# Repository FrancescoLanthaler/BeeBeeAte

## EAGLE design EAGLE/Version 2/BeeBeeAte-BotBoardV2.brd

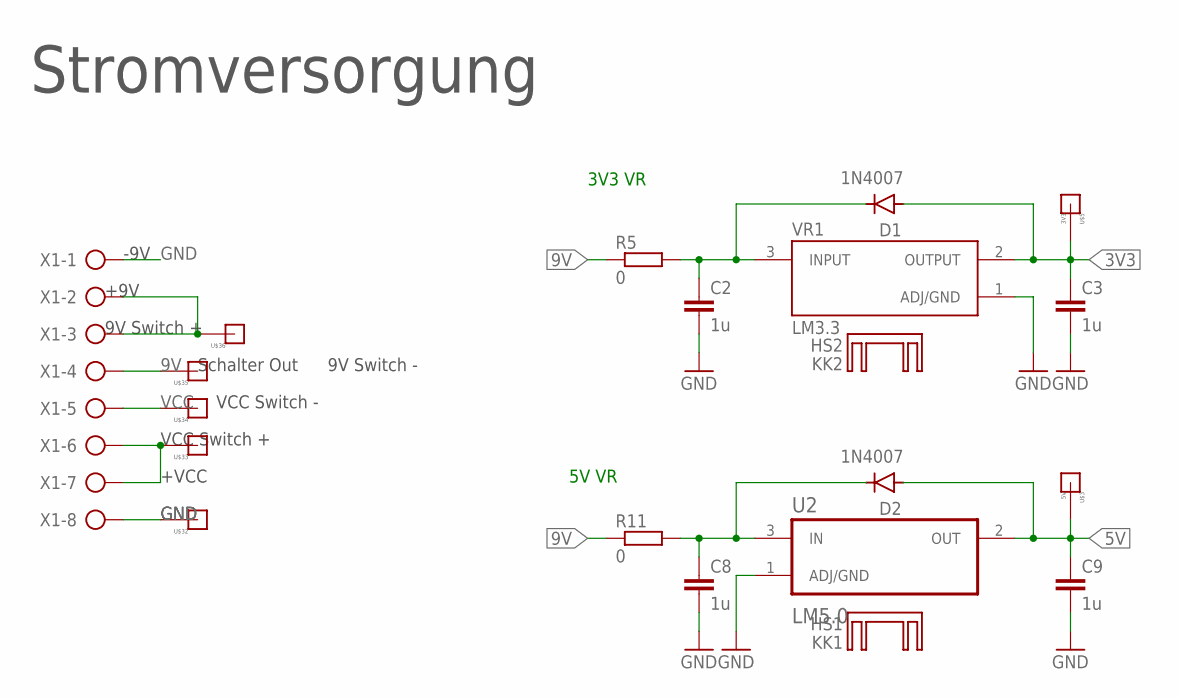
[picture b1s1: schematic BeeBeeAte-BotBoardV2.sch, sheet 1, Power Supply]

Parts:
C2, C3, C8, C9: 1u; C0805
D1, D2: 1N4007; DO-41
KK1: HS1; SK95-2M3
KK2: HS2; SK95-2M3
R5, R11: 0; R0805
U2: LM5.0; TO254P1054X470X1955-3
U$3: 5V; MESSPAD
U$5: 3V3; MESSPAD
U$32, U$33, U$34, U$35, U$36: MESSPAD
VR1: LM3.3; TO254P1054X470X1955-3
X1: +9V; AK300/8

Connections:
3V3: C3.1, D1.A, U$5.MSP, VR1.2 (OUTPUT); also elsewhere on the board
5V: C9.1, D2.A, U2.2 (OUT), U$3.MSP; also elsewhere on the board
9V: R5.1, R11.1, U$35.MSP, X1.4
+VCC: U$33.MSP, X1.6, X1.7
GND: C2.2, C3.2, C8.2, C9.2, U2.1 (ADJ/GND), U$32.MSP, VR1.1 (ADJ/GND), X1.1, X1.8; also elsewhere on the board
unnamed: C2.1, D1.C, R5.2, VR1.3 (INPUT)
unnamed: C8.1, D2.C, R11.2, U2.3 (IN)
unnamed: U$36.MSP, X1.2, X1.3
VCC: U$34.MSP, X1.5; also elsewhere on the board

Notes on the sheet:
5V VR
3V3 VR
Stromversorgung
Schalter Out
9V Switch +
9V Switch -
+9V
-9V
VCC Switch -
+VCC
VCC Switch +

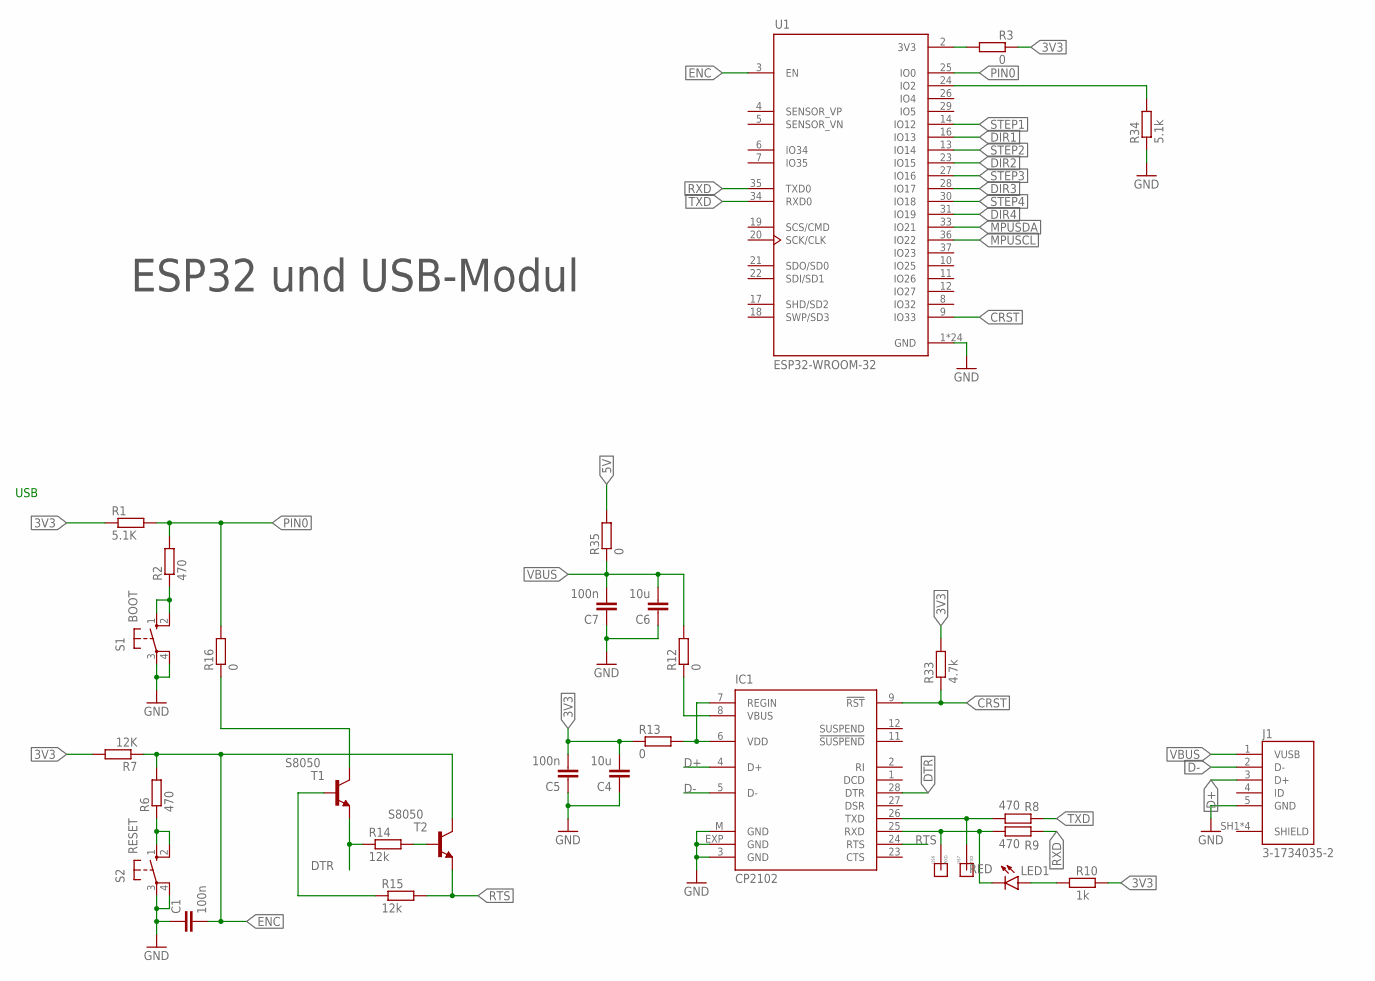
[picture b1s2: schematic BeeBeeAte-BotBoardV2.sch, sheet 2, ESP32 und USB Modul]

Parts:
C1, C5, C7: 100n; C0805
C4, C6: 10u; C0805
IC1: CP2102; MLP28
J1: 3-1734035-2; TE_3-1734035-2
LED1: RED; CHIP-LED0805
R1: 5.1K; R0805
R2, R6, R8, R9: 470; R0805
R3, R12, R13, R16, R35: 0; R0805
R7: 12K; R0805
R10: 1k; R0805
R14, R15: 12k; R0805
R33: 4.7k; R0805
R34: 5.1k; R0805
S1: BOOT; B3F-10XX
S2: RESET; B3F-10XX
T1, T2: S8050; SOT23-BEC
U1: ESP32-WROOM-32; MODULE_ESP32-WROOM-32
U$6: RXD; MESSPAD
U$7: TXD; MESSPAD

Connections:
3V3: C4.2, C5.2, R1.1, R3.2, R7.2, R10.2, R13.1, R33.2; also elsewhere on the board
5V: R35.2; also elsewhere on the board
CRST: IC1.9 (!RST), R33.1, U1.9 (IO33)
D+: IC1.4 (D+), J1.3 (D+)
D-: IC1.5 (D-), J1.2 (D-)
DIR1: U1.16 (IO13); also elsewhere on the board
DIR2: U1.23 (IO15); also elsewhere on the board
DIR3: U1.28 (IO17); also elsewhere on the board
DIR4: U1.31 (IO19); also elsewhere on the board
DTR: IC1.28 (DTR), R14.1, T1.E
ENC: C1.2, R6.2, R7.1, T2.C, U1.3 (EN)
GND: C1.1, C4.1, C5.1, C6.1, C7.1, IC1.3 (GND), IC1.EXP (GND), IC1.M (GND), J1.5 (GND), R34.1, S1.3, S1.4 (P1), S2.3, S2.4 (P1), U1.1 (GND), U1.15 (GND), U1.38 (GND), U1.39_1 (GND), U1.39_2 (GND), U1.39_3 (GND), U1.39_4 (GND), U1.39_5 (GND), U1.39_6 (GND), U1.39_7 (GND), U1.39_8 (GND), U1.39_9 (GND), U1.39_10 (GND), U1.39_11 (GND), U1.39_12 (GND), U1.39_13 (GND), U1.39_14 (GND), U1.39_15 (GND), U1.39_16 (GND), U1.39_17 (GND), U1.39_18 (GND), U1.39_19 (GND), U1.39_20 (GND), U1.39_21 (GND); also elsewhere on the board
MPUSCL: U1.36 (IO22); also elsewhere on the board
MPUSDA: U1.33 (IO21); also elsewhere on the board
unnamed: R2.1, S1.1 (S), S1.2 (S1)
unnamed: R6.1, S2.1 (S), S2.2 (S1)
unnamed: IC1.25 (RXD), LED1.C, R9.1, U$6.MSP
unnamed: LED1.A, R10.1
unnamed: IC1.26 (TXD), R8.1, U$7.MSP
unnamed: IC1.6 (VDD), IC1.7 (REGIN), R13.2
unnamed: IC1.8 (VBUS), R12.1
unnamed: R14.2, T2.B
unnamed: R15.1, T1.B
unnamed: R34.2, U1.24 (IO2)
unnamed: R3.1, U1.2 (3V3)
PIN0: R1.2, R2.2, R16.2, U1.25 (IO0)
PIN1: R16.1, T1.C
RTS: IC1.24 (RTS), R15.2, T2.E
RXD: R9.2, U1.35 (TXD0)
STEP1: U1.14 (IO12); also elsewhere on the board
STEP2: U1.13 (IO14); also elsewhere on the board
STEP3: U1.27 (IO16); also elsewhere on the board
STEP4: U1.30 (IO18); also elsewhere on the board
TXD: R8.2, U1.34 (RXD0)
VBUS: C6.2, C7.2, J1.1 (VUSB), R12.2, R35.1

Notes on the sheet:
USB
ESP32 und USB-Modul

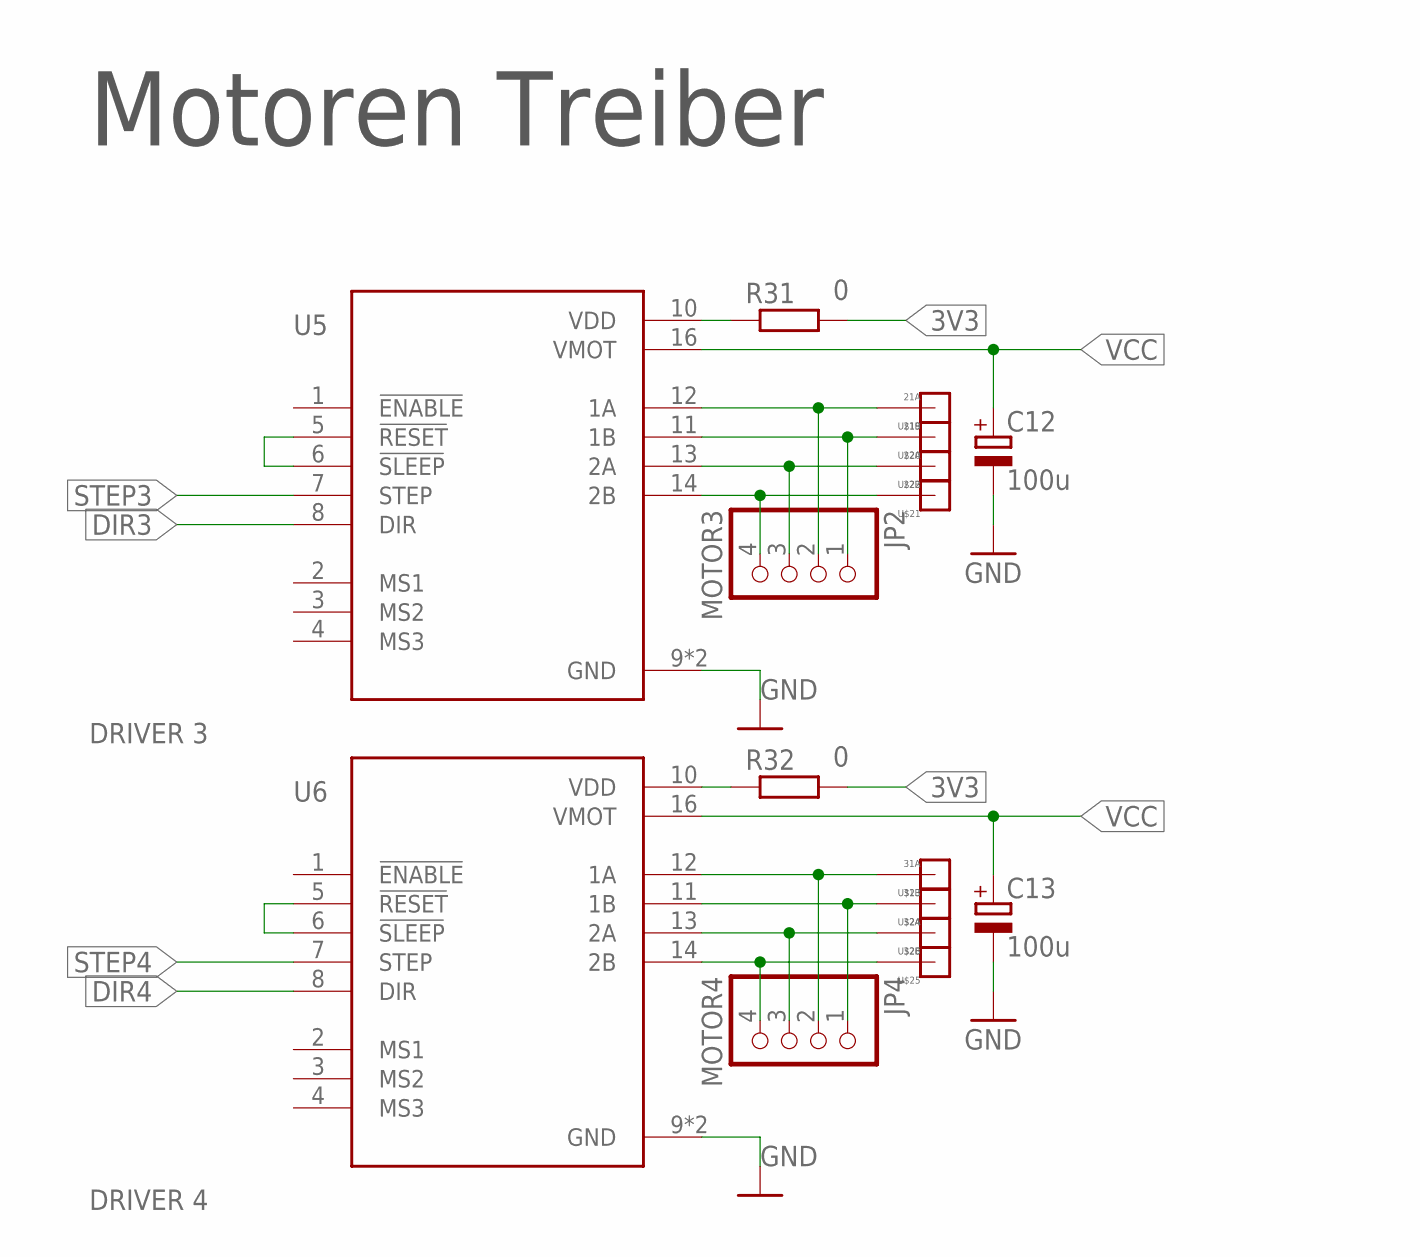
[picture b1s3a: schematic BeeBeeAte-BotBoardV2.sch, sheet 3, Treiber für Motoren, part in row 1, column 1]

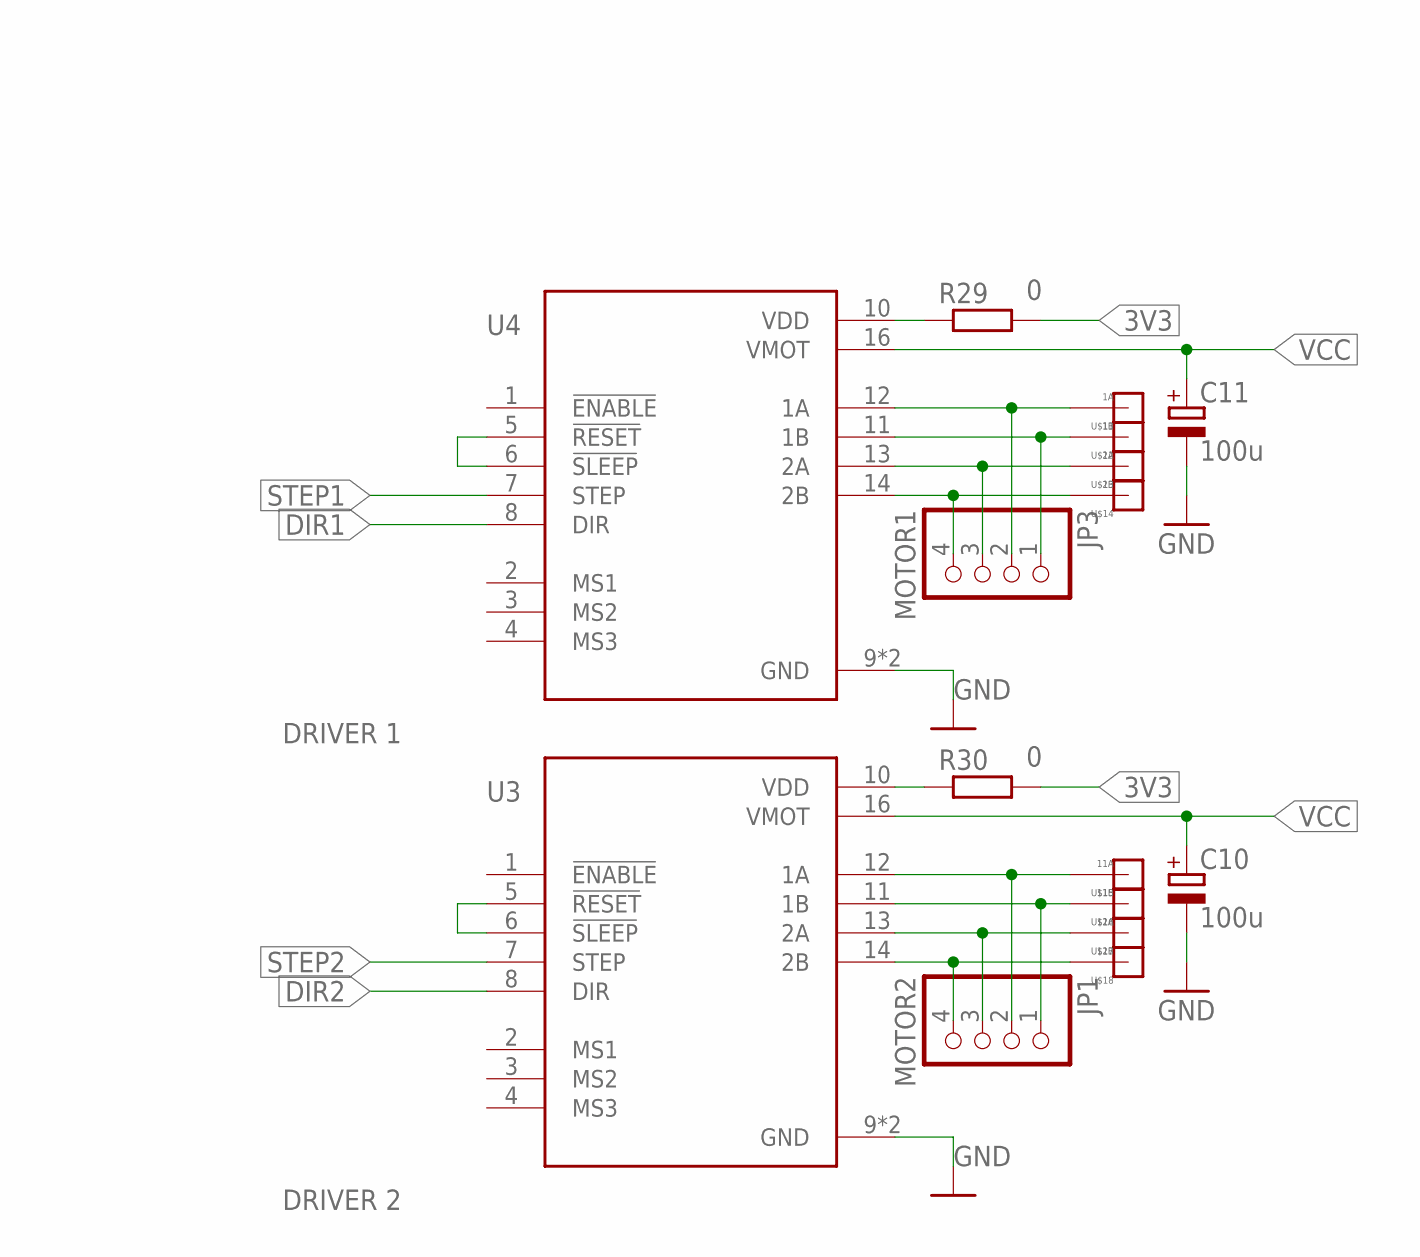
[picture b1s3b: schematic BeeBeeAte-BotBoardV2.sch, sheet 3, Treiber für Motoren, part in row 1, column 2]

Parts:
C10, C11, C12, C13: 100u; 153CLV-0605
JP1: MOTOR2; 1X04
JP2: MOTOR3; 1X04
JP3: MOTOR1; 1X04
JP4: MOTOR4; 1X04
R29, R30, R31, R32: 0; R0805
U3: DRIVER 2; MODULE_A4988_STEPPER_MOTOR_DRIVER_CARRIER
U4: DRIVER 1; MODULE_A4988_STEPPER_MOTOR_DRIVER_CARRIER
U5: DRIVER 3; MODULE_A4988_STEPPER_MOTOR_DRIVER_CARRIER
U6: DRIVER 4; MODULE_A4988_STEPPER_MOTOR_DRIVER_CARRIER
U$11: 1A; MESSPAD
U$12: 1B; MESSPAD
U$13: 2A; MESSPAD
U$14: 2B; MESSPAD
U$15: 11A; MESSPAD
U$16: 11B; MESSPAD
U$17: 12A; MESSPAD
U$18: 12B; MESSPAD
U$19: 21A; MESSPAD
U$20: 21B; MESSPAD
U$21: 22B; MESSPAD
U$22: 22A; MESSPAD
U$23: 31A; MESSPAD
U$24: 31B; MESSPAD
U$25: 32B; MESSPAD
U$26: 32A; MESSPAD

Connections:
3V3: R29.2, R30.2, R31.2, R32.2; also elsewhere on the board
DIR1: U4.8 (DIR); also elsewhere on the board
DIR2: U3.8 (DIR); also elsewhere on the board
DIR3: U5.8 (DIR); also elsewhere on the board
DIR4: U6.8 (DIR); also elsewhere on the board
GND: C10.-, C11.-, C12.-, C13.-, U3.9 (GND), U3.15 (GND), U4.9 (GND), U4.15 (GND), U5.9 (GND), U5.15 (GND), U6.9 (GND), U6.15 (GND); also elsewhere on the board
unnamed: R30.1, U3.10 (VDD)
unnamed: JP1.2, U3.12 (1A), U$15.MSP
unnamed: JP1.1, U3.11 (1B), U$16.MSP
unnamed: JP1.3, U3.13 (2A), U$17.MSP
unnamed: JP1.4, U3.14 (2B), U$18.MSP
unnamed: U3.5 (!RESET), U3.6 (!SLEEP)
unnamed: R29.1, U4.10 (VDD)
unnamed: JP2.2, U5.12 (1A), U$19.MSP
unnamed: JP2.1, U5.11 (1B), U$20.MSP
unnamed: JP2.3, U5.13 (2A), U$22.MSP
unnamed: JP2.4, U5.14 (2B), U$21.MSP
unnamed: JP3.2, U4.12 (1A), U$11.MSP
unnamed: JP3.1, U4.11 (1B), U$12.MSP
unnamed: JP3.3, U4.13 (2A), U$13.MSP
unnamed: U5.5 (!RESET), U5.6 (!SLEEP)
unnamed: R31.1, U5.10 (VDD)
unnamed: R32.1, U6.10 (VDD)
unnamed: JP3.4, U4.14 (2B), U$14.MSP
unnamed: U4.5 (!RESET), U4.6 (!SLEEP)
unnamed: JP4.2, U6.12 (1A), U$23.MSP
unnamed: JP4.1, U6.11 (1B), U$24.MSP
unnamed: JP4.3, U6.13 (2A), U$26.MSP
unnamed: JP4.4, U6.14 (2B), U$25.MSP
unnamed: U6.5 (!RESET), U6.6 (!SLEEP)
STEP1: U4.7 (STEP); also elsewhere on the board
STEP2: U3.7 (STEP); also elsewhere on the board
STEP3: U5.7 (STEP); also elsewhere on the board
STEP4: U6.7 (STEP); also elsewhere on the board
VCC: C10.+, C11.+, C12.+, C13.+, U3.16 (VMOT), U4.16 (VMOT), U5.16 (VMOT), U6.16 (VMOT); also elsewhere on the board

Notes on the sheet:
Motoren Treiber

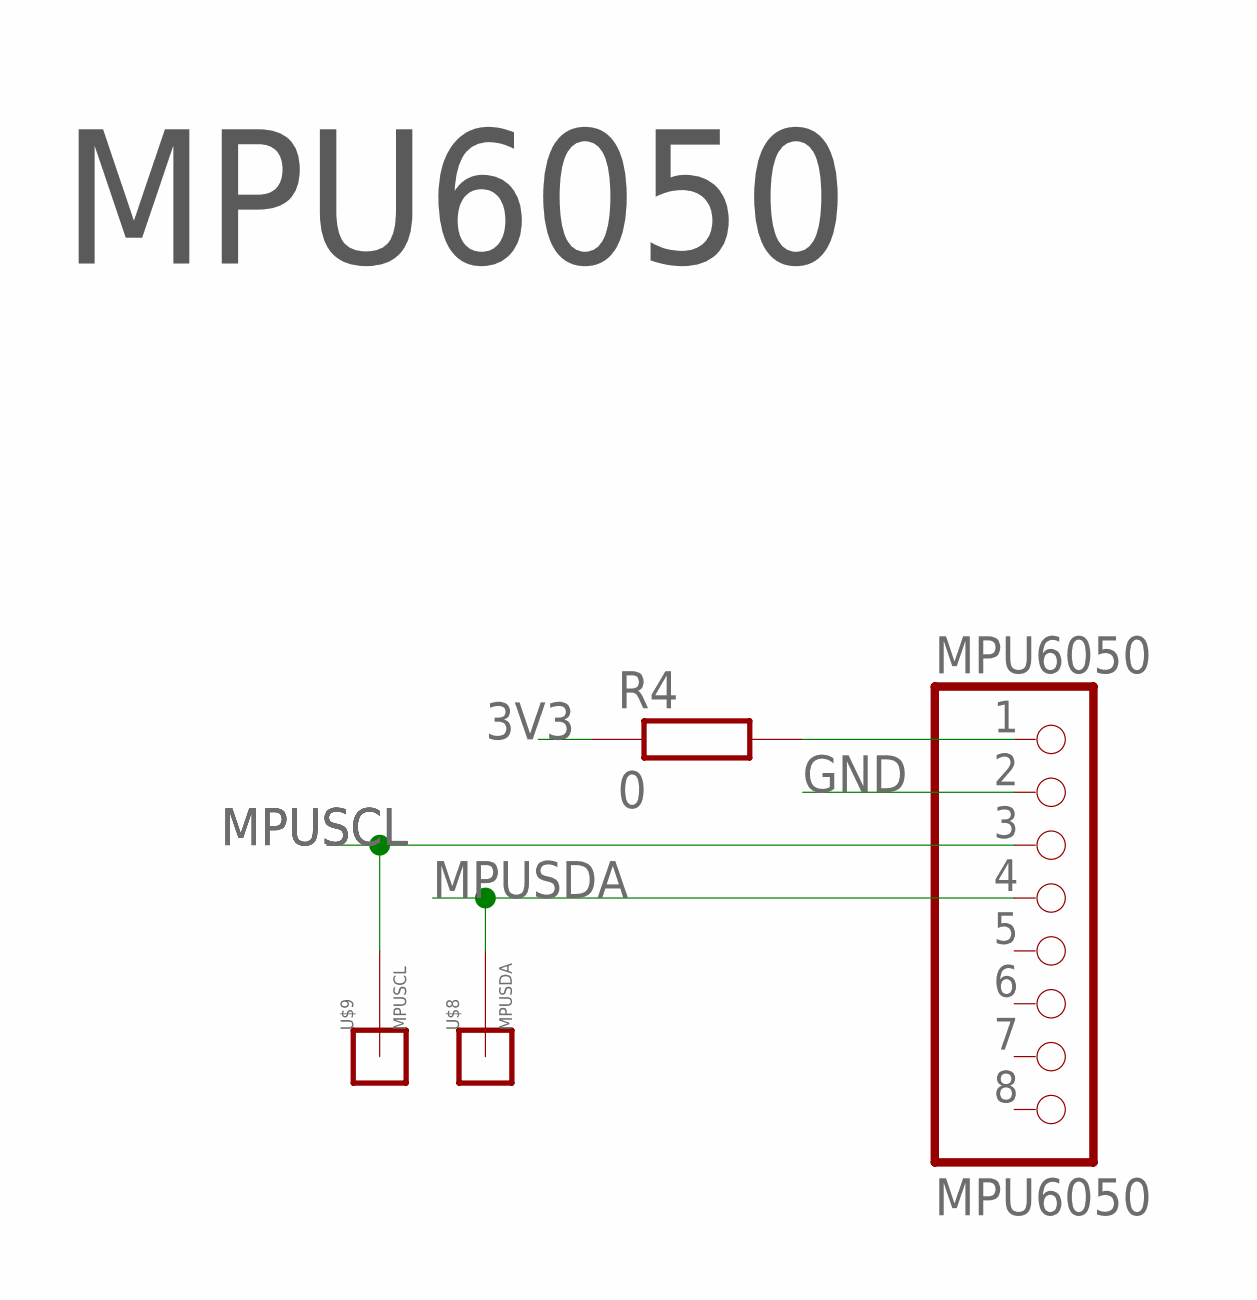
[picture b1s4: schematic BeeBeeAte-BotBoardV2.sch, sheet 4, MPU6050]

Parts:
MPU6050: MPU6050; 1X08
R4: 0; R0805
U$8: MPUSDA; MESSPAD
U$9: MPUSCL; MESSPAD

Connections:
3V3: R4.1; also elsewhere on the board
GND: MPU6050.2; also elsewhere on the board
MPUSCL: MPU6050.3, U$9.MSP; also elsewhere on the board
MPUSDA: MPU6050.4, U$8.MSP; also elsewhere on the board
unnamed: MPU6050.1, R4.2

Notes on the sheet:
MPU6050

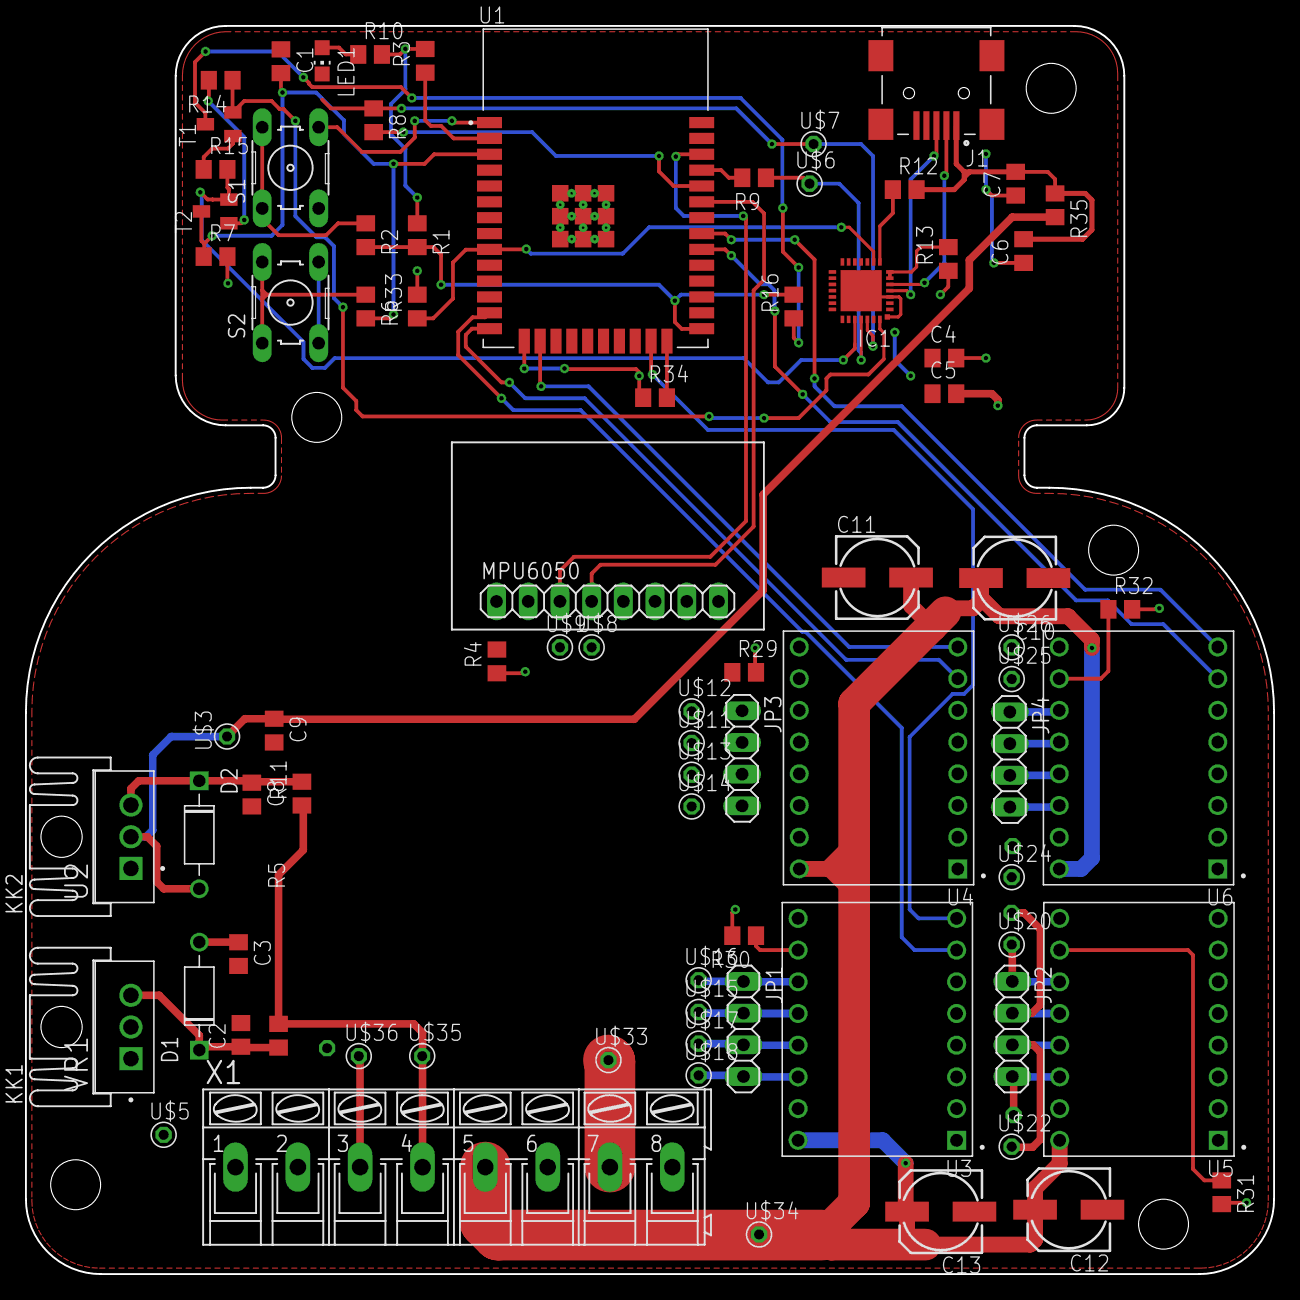
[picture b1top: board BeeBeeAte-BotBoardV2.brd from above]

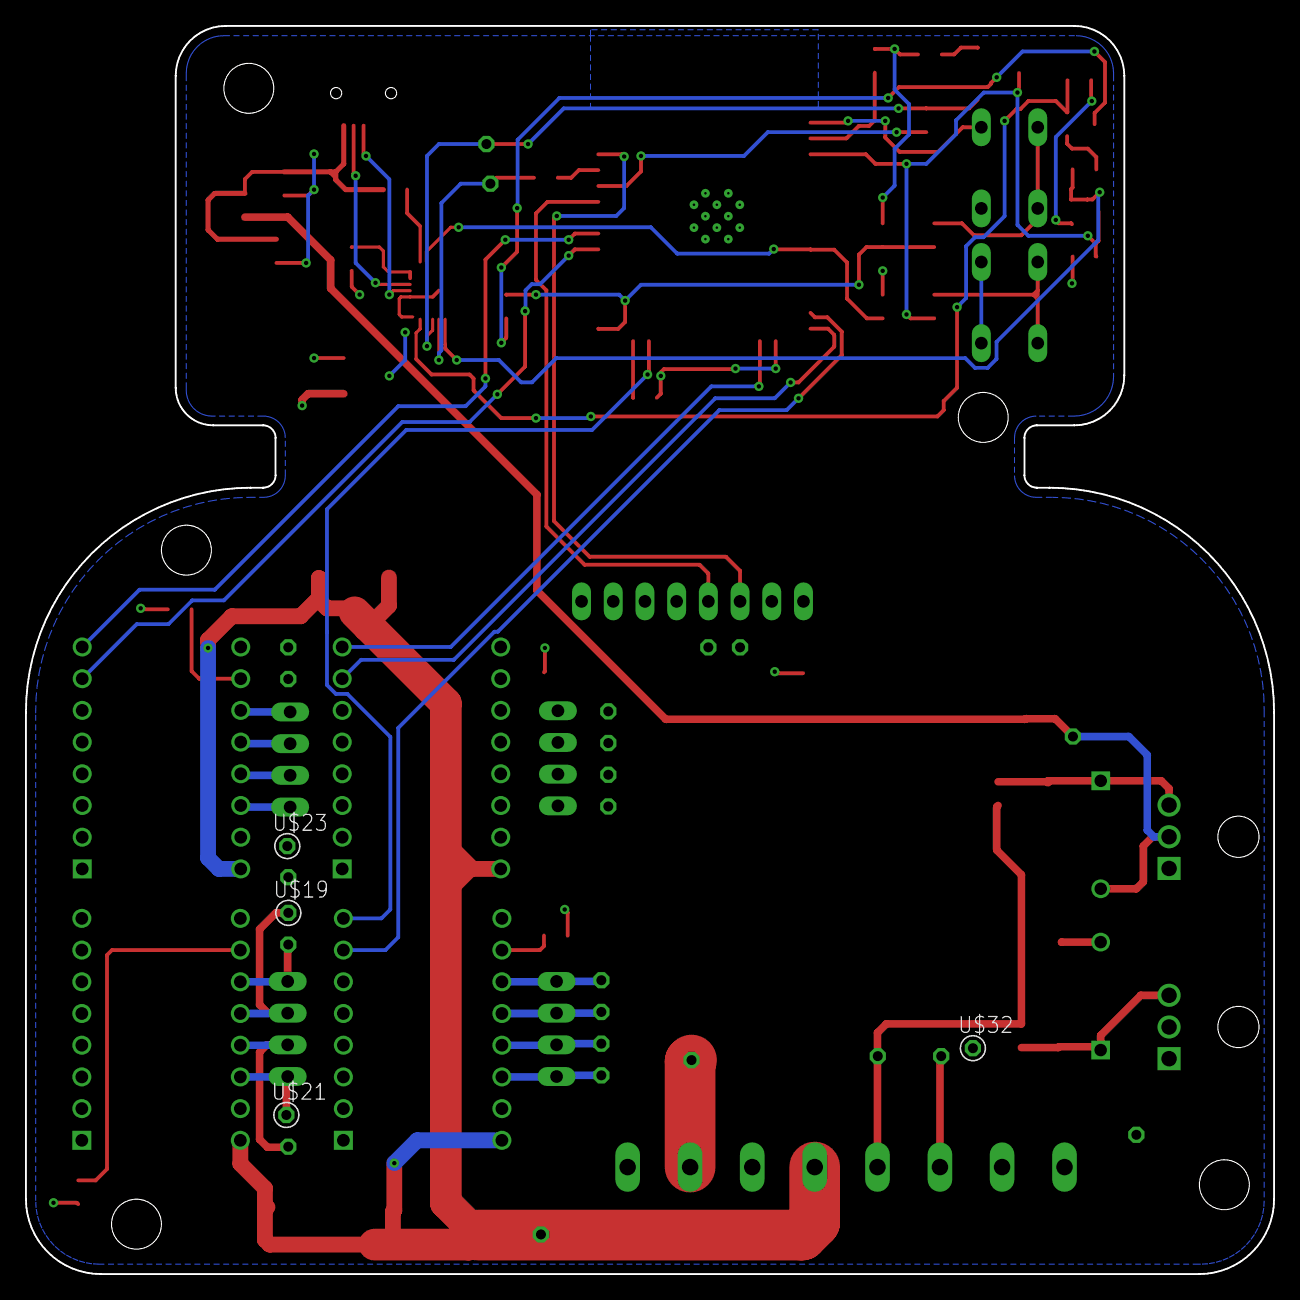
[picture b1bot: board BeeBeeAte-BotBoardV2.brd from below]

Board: 2 copper layers, 100.0 x 100.0 mm, 87 parts (4 on the bottom side), 66 nets.

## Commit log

2021-10-26 First remote
2021-10-26 Renaming files
2021-10-26 Added Remote
2021-10-26 added gitignore
2021-10-26 Border put in milling layer
2021-10-27 Completed BOM and CPL
2021-10-27 Changed Gerber File to tValue
2021-10-27 Added Logo to remote and created GERBER, BOM and CPL for remote
2021-10-28 temp file
2021-11-01 Added 3,7V battery
2021-11-06 Added 3D Files and modified Board
2021-11-08 Checked by teacher and fixed
2021-11-17 MILESTONE: PCB Ordered
2021-12-13 Added Code
2021-12-13 Added Header files (errors)
2021-12-15 Added Motors
2021-12-15 Added Motorpins defines
2021-12-21 Added different files. Formula to calculate speed and function to control motors
2022-01-17 Erste Version des Algorythmus abgeschlossen
2022-01-29 Updated code and started editing PCB
2022-02-07 New Board
2022-02-16 Version to make better
2022-02-16 Tried with PID loop
2022-04-07 Halb Funktionierend mit PID-Regler
2022-04-22 Harsh but functioning
2022-04-28 Functioning version
2022-05-05 Final Version
2022-05-13 actually most definetly the final version
